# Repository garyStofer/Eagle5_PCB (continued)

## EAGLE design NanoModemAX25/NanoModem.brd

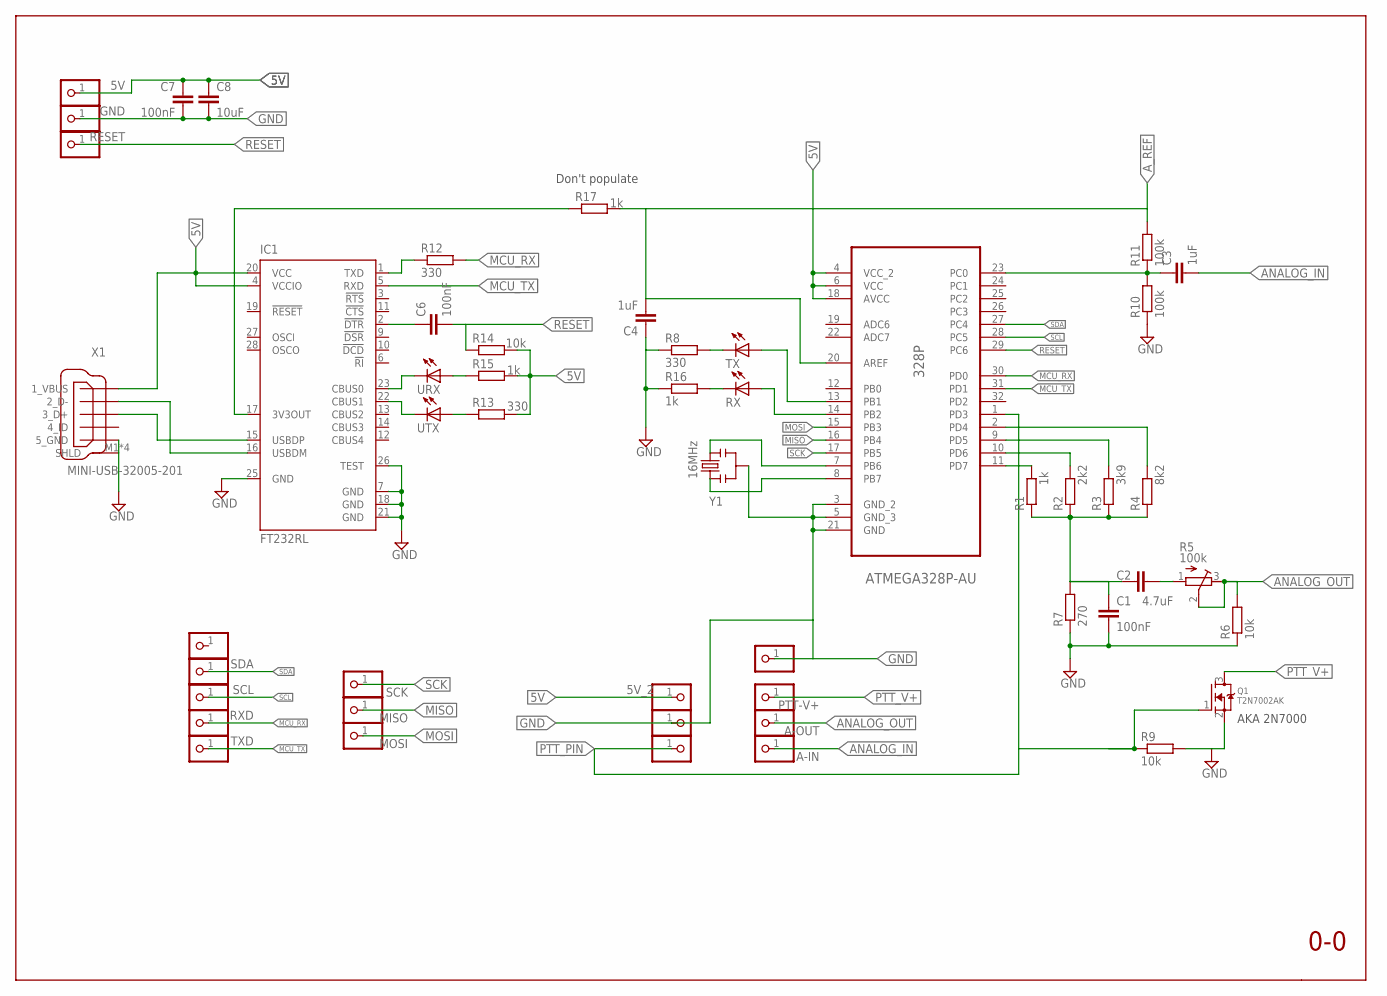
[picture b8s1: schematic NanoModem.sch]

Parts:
3V3, 5V, 5V_2: PINHD-1X1; 1X01
328P: ATMEGA328P-AU; QFP80P900X900X120-32N
A-IN: PINHD-1X1; 1X01
A-OUT: PINHD-1X1; 1X01
C1, C6, C7: 100nF; C0603
C2: 4.7uF; C0805
C3, C4: 1uF; C0603
C8: 10uF; C1210
GND, GND1, GND2: PINHD-1X1; 1X01
IC1: FT232RL; SSOP28
MISO: PINHD-1X1; 1X01
MOSI: PINHD-1X1; 1X01
PTT-PIN: PINHD-1X1; 1X01
PTT-V+: PINHD-1X1; 1X01
Q1: T2N7002AK; SOT23
R1, R15, R16, R17: 1k; R0603
R2: 2k2; R0603
R3: 3k9; R0603
R4: 8k2; R0603
R5: 100k; RTRIM3339P
R6, R9, R14: 10k; R0603
R7: 270; R0603
R8, R12, R13: 330; R0603
R10, R11: 100k; R0603
RESET: PINHD-1X1; 1X01
RX: LED_ESML0603; LED_SML0603
RXD: PINHD-1X1; 1X01
SCK: PINHD-1X1; 1X01
SCL: PINHD-1X1; 1X01
SDA: PINHD-1X1; 1X01
TX: LED_ESML0603; LED_SML0603
TXD: PINHD-1X1; 1X01
URX: LED_ESML0603; LED_SML0603
UTX: LED_ESML0603; LED_SML0603
X1: MINI-USB-32005-201; 32005-201
Y1: 16MHz; RESONATOR-SMD

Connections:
3V3: IC1.17 (3V3OUT), R17.1
5V: 5V.1, 5V_2.1, 328P.4 (VCC_2), 328P.6 (VCC), 328P.18 (AVCC), C7.2, C8.1, IC1.4 (VCCIO), IC1.20 (VCC), R13.2, R14.2, R15.2, X1.1_VBUS
ADC0: 328P.23 (PC0), C3.1, R10.2, R11.1
ANALOG_IN: A-IN.1, C3.2
ANALOG_OUT: A-OUT.1, R5.2 (S), R5.3 (E), R6.2
A_REF: 328P.20 (AREF), C4.2, R11.2, R17.2
DAC_1: 328P.2 (PD4), R4.2
DAC_2: 328P.9 (PD5), R3.2
DAC_3: 328P.10 (PD6), R2.2
DAC_4: 328P.11 (PD7), R1.2
DTR: C6.1, IC1.2 (!DTR)
FTDI_TX: IC1.1 (TXD), R12.1
GND: 328P.3 (GND_2), 328P.5 (GND_3), 328P.21 (GND), C1.2, C4.1, C7.1, C8.2, GND.1, GND1.1, GND2.1, IC1.7 (GND), IC1.18 (GND), IC1.21 (GND), IC1.25 (GND), IC1.26 (TEST), Q1.2 (S), R6.1, R7.1, R8.1, R9.2, R10.1, R16.1, X1.5_USB_GND (5_GND), X1.M1 (SHLD), X1.M2 (SHLD), X1.M3 (SHLD), X1.M4 (SHLD), Y1.2
MCU_RX: 328P.30 (PD0), R12.2, RXD.1
MCU_TX: 328P.31 (PD1), IC1.5 (RXD), TXD.1
MISO: 328P.16 (PB4), MISO.1
MOSI: 328P.15 (PB3), MOSI.1
unnamed: R13.1, UTX.A
unnamed: IC1.23 (CBUS0), URX.C
unnamed: IC1.22 (CBUS1), UTX.C
unnamed: R15.1, URX.A
unnamed: 328P.7 (PB6), Y1.3
unnamed: C1.1, C2.2, R1.1, R2.1, R3.1, R4.1, R7.2
unnamed: R16.2, RX.C
unnamed: 328P.14 (PB2), RX.A
unnamed: 328P.13 (PB1), TX.A
unnamed: C2.1, R5.1 (A)
unnamed: 328P.8 (PB7), Y1.1
unnamed: R8.2, TX.C
unnamed: IC1.15 (USBDP), X1.3_D+
unnamed: IC1.16 (USBDM), X1.2_D-
PTT_PIN: 328P.1 (PD3), PTT-PIN.1, Q1.1 (G), R9.1
PTT_V+: PTT-V+.1, Q1.3 (D)
RESET: 328P.29 (PC6), C6.2, R14.1, RESET.1
SCK: 328P.17 (PB5), SCK.1
SCL: 328P.28 (PC5), SCL.1
SDA: 328P.27 (PC4), SDA.1

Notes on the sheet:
0-0
AKA 2N7000
Don't populate

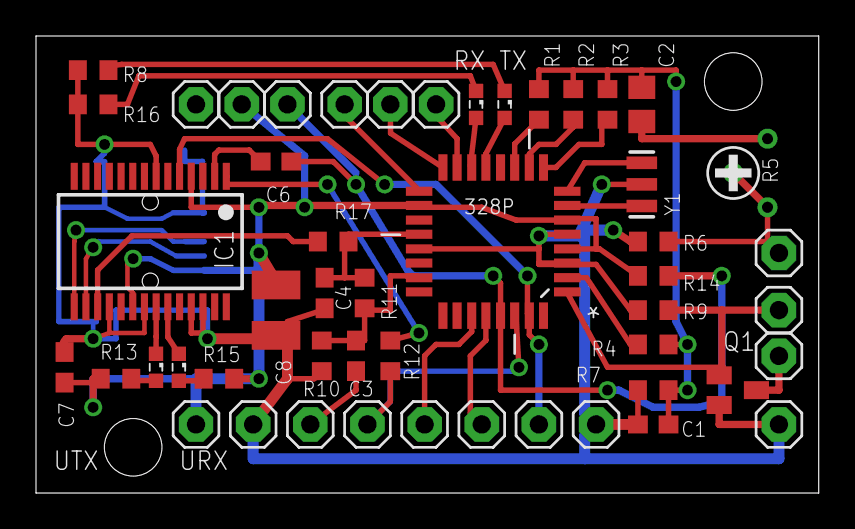
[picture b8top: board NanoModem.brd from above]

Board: 2 copper layers, 43.5 x 25.4 mm, 51 parts (1 on the bottom side), 37 nets.

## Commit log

2011-06-11 Nintendo joystick to USB converter
2013-03-04 added all the small boards, renamed Wifi module as RH and LH version
2013-03-08 updated BOM with all prices- As Checked in to BATCH PCB
2013-04-25 Initial version check in for dot clock LED fan out board
2013-04-25 Wind speed board and base station rework to rev HW 1.2
2013-07-08 initial check in
2013-07-08 moved a trace slightly
2013-07-15 updated schematic for reset line and PNP transistor
2013-07-15 added zip file as sent to PCB
2013-09-24 Revision B.1
2013-09-24 added smd led_con1 brd and sch
2013-11-26 Changed to RJ11 connector for Baro_temp_hyg on base board -- Cleaned up some silk screen stuff Added new RJ11 based Baro_Temp_Hyg board layout
2013-12-26 added SILabs Hygrometer board Added frames to the schematics
2014-03-04 Added multiple new boards - H-pwrdist- Insp_Wind_enc, 5040 etc..
2014-03-05 Deleted all of WiFi_WX_Station Moved to repository All_WiFi_WX/trunk/Hardware
2015-01-12 Changed to accommodate easier wiring of switch and output
2015-07-29 Added more projects to the lump
2015-09-28 finished design of PCB and uploaded to OSH PCB
2015-09-28 labeled connectors
2015-10-29 Revised to rev 0.1
2015-11-11 recheck in after GIT screwed up the files
2015-11-13 removed LCD_AC_Instr -- moved to it;s own repo together with the firmware and cad
2016-03-02 moved / removed old weather station files
2016-03-09 Added forgotten folders
2017-02-24 added Nano Modem some modifications on nRFPatch board
2018-06-07 added RV8 trim relays schematic and board
2018-06-07 no change
2018-06-07 added Lundin's schematic, RV8 trim relay schemtic and board, Sonoma protoboard
2018-10-04 added power down option for MP3 and USB connector
2018-10-04 added picture file
2018-10-30 hopefully last changes
2018-10-30 Board that constrains the power Triac for the lamp
2018-10-30 some changes to the APRS modem board
2018-10-30 added simple 5V LDO pcb
2018-10-30 added AOA PCB
2018-10-30 added latest source with pre-compiled HEX files from Mark Quist added standalone Averdude programmer tools to flash using Arduino style bootloader added some how to txt files
2018-10-30 moved NanoModemAX25 to its own repo to APRS_NanoModem
2018-10-31 Removed ArduinoLundin -- moved to it's own repo with all the rest of the code
2019-10-31 Added Nrf24 Arduino Mysensor node
2019-11-21 nRF_MySensor board: Added resistor position for external pull up on PC0. Added spare GND and VCC solder points. Fixed R2/R3 values swapped Added more detailed build option instructions.
2019-11-21 nRF_arduino_patch: Fixed swapped values on R2/R3
2019-11-22 nrfMysensor.brd: Fixed font on version indication that was interpreted bigger by OSHPARK pcb
